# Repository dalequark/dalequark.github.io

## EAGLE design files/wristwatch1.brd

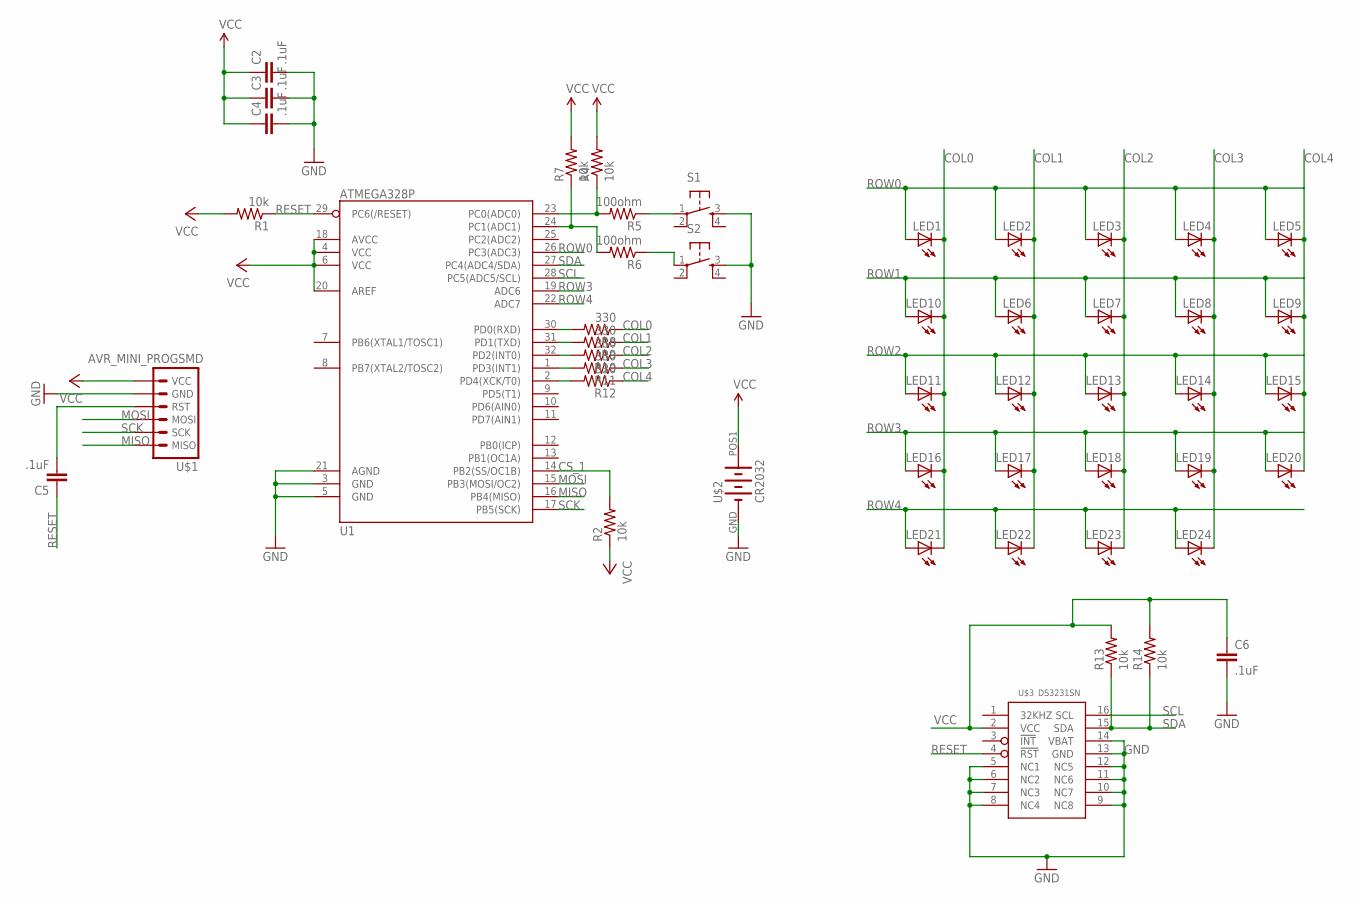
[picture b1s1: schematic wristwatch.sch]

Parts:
C2, C3, C4, C5, C6: .1uF; 0805
LED1, LED2, LED3, LED4, LED5, LED6, LED7, LED8, LED9, LED10, LED11, LED12, LED13, LED14, LED15, LED16, LED17, LED18, LED19, LED20, LED21, LED22, LED23, LED24: LEDCHIP-LED0805; CHIP-LED0805
R1, R2, R4, R7, R13, R14: 10k; SPARKFUN_0805
R5, R6: 100ohm; SPARKFUN_0805
R8, R9, R10, R11, R12: 330; SPARKFUN_0805
S1, S2: TAC_SWITCHSMD; TACTILE-SWITCH-SMD
U1: ATMEGA328P; TQFP32-08
U$1: AVR_MINI_PROGSMD; AVR_MINI_PROG
U$2: CR2032; CR2032-BAT-HLD
U$3: DS3231SN; SO16L

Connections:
COL0: LED1.C, LED10.C, LED11.C, LED16.C, LED21.C, R8.1
COL1: LED2.C, LED6.C, LED12.C, LED17.C, LED22.C, R9.1
COL2: LED3.C, LED7.C, LED13.C, LED18.C, LED23.C, R10.1
COL3: LED4.C, LED8.C, LED14.C, LED19.C, LED24.C, R11.1
COL4: LED5.C, LED9.C, LED15.C, LED20.C, R12.1
CS_1: R2.2, U1.14 (PB2(SS/OC1B))
GND: C2.2, C3.2, C4.2, C6.2, S1.3, S2.3, U1.3 (GND), U1.5 (GND), U1.21 (AGND), U$1.2 (GND), U$2.GND (-), U$3.5 (NC1), U$3.6 (NC2), U$3.7 (NC3), U$3.8 (NC4), U$3.9 (NC8), U$3.10 (NC7), U$3.11 (NC6), U$3.12 (NC5), U$3.13 (GND), U$3.14 (VBAT); also elsewhere on the board
MISO: U1.16 (PB4(MISO)), U$1.6 (MISO)
MOSI: U1.15 (PB3(MOSI/OC2)), U$1.4 (MOSI)
unnamed: C5.2, U$1.3 (RST)
unnamed: R4.1, R5.2, U1.23 (PC0(ADC0))
unnamed: R5.1, S1.1
unnamed: R6.1, S2.1
unnamed: R8.2, U1.30 (PD0(RXD))
unnamed: R6.2, R7.1, U1.24 (PC1(ADC1))
unnamed: R9.2, U1.31 (PD1(TXD))
unnamed: R10.2, U1.32 (PD2(INT0))
unnamed: R11.2, U1.1 (PD3(INT1))
unnamed: R12.2, U1.2 (PD4(XCK/T0))
RESET: C5.1, R1.1, U1.29 (PC6(/RESET)), U$3.4 (!RST)
ROW0: LED1.A, LED2.A, LED3.A, LED4.A, LED5.A, U1.26 (PC3(ADC3))
ROW1: LED6.A, LED7.A, LED8.A, LED9.A, LED10.A
ROW2: LED11.A, LED12.A, LED13.A, LED14.A, LED15.A
ROW3: LED16.A, LED17.A, LED18.A, LED19.A, LED20.A, U1.19 (ADC6)
ROW4: LED21.A, LED22.A, LED23.A, LED24.A, U1.22 (ADC7)
SCK: U1.17 (PB5(SCK)), U$1.5 (SCK)
SCL: U1.28 (PC5(ADC5/SCL)), U$3.16 (SCL)
SDA: R13.1, R14.1, U1.27 (PC4(ADC4/SDA)), U$3.15 (SDA)
VCC: C2.1, C3.1, C4.1, C6.1, R1.2, R2.1, R4.2, R7.2, R13.2, R14.2, U1.4 (VCC), U1.6 (VCC), U1.18 (AVCC), U1.20 (AREF), U$1.1 (VCC), U$2.POS1 (+), U$3.2 (VCC); also elsewhere on the board

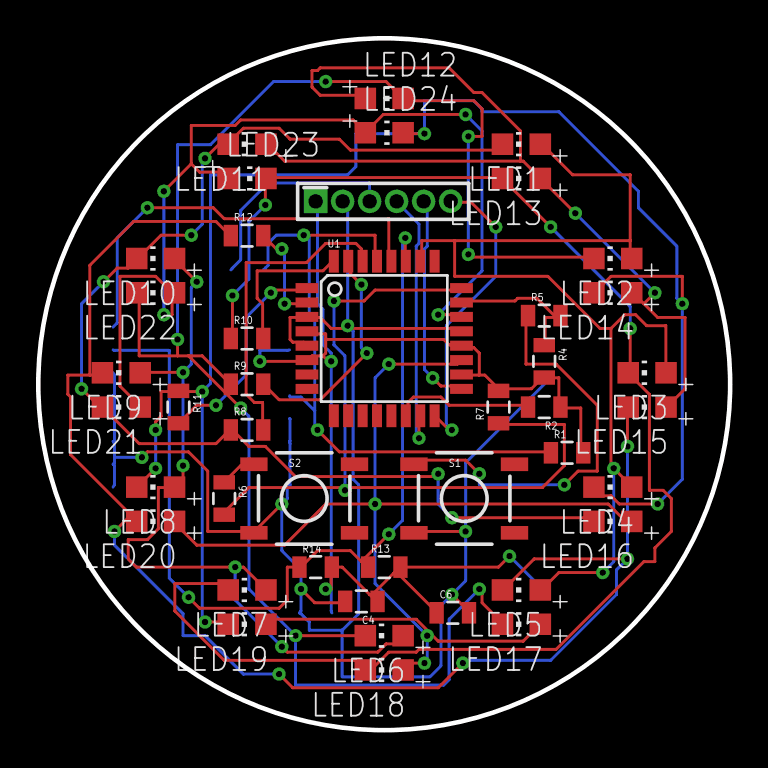
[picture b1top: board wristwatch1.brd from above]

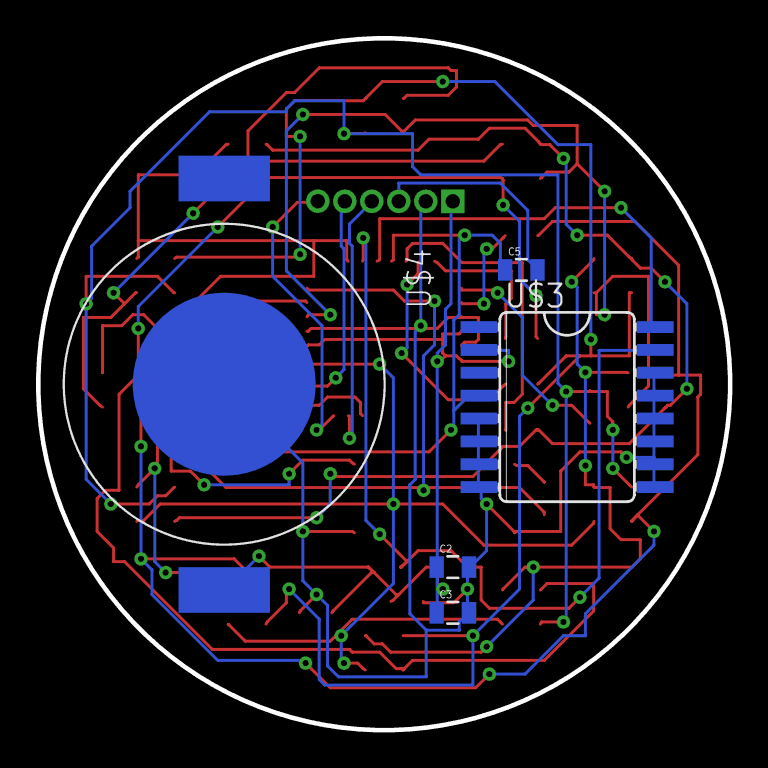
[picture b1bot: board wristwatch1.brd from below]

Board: 2 copper layers, 38.4 x 38.4 mm, 48 parts (5 on the bottom side), 29 nets.

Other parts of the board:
U$4: CR2032; CR2032-BAT-HLD

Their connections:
GND: U$4.NEG; also elsewhere on the board
VCC: U$4.POS1; also elsewhere on the board

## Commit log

2013-09-16 Ugh. trying to deal with the problem of integrating serverside and clientside templating. Very difficult
2013-09-25 new theme
2013-09-25 new blog
2014-01-27 prettier
2014-01-27 caps
2014-06-04 Hyde
2014-06-20 changed cname
2014-07-01 Added an article
2014-07-01 fixed masthead
2014-07-01 temp cname
2014-07-01 temp cname2
2014-07-02 font
2014-07-03 added cname
2014-07-03 fixed about link
2014-07-03 fixed 404
2014-07-03 no really
2014-07-03 liquid
2014-07-03 kramdown
2014-11-09 changed a few things, added posts
2014-11-11 Added some article headers
2014-11-11 removed sym link
2014-11-13 working on making tags selectable
2014-11-17 changed font
2014-11-26 added photos directory
2014-11-28 Switching to different theme
2014-11-28 switched themes
2014-11-28 Lookin good
2014-11-28 update yaml with unquarked
2014-12-03 added beaglecahce pics
2014-12-07 filled in blog articles
2014-12-17 updated stuff with reasonable stuff
2014-12-22 updated neuromancer
2014-12-22 minor author footer typo
2014-12-22 another little typo
2015-01-02 updated pixel necklace
2015-05-05 one minor change to neuromancer

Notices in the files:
parts and their libraries:
SparkFun-DigitalIC: Licensing: Creative Commons ShareAlike 4.0 International - https://creativecommons.org/licenses/by-sa/4.0
